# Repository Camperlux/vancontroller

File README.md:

# VanController

A 12 V campervan controller board: ESP32-S3 with 6 fused relays, 6 fused PWM dimmers, CAN, RS485, GPS, an accelerometer and 2 water-level inputs, plus a 3D-printable enclosure. Designed in KiCad 10.

| | |
|---|---|
| **Revision** | 0.3a |
| **Status** | Design complete (ERC and DRC clean). Prototype order with PCBWay under engineering review since 2026-10-06; see [docs/ORDER_LOG.md](docs/ORDER_LOG.md). Not yet verified on hardware. |
| **Board** | 230 × 135 mm, 4 layers (In1 = GND plane, In2 = +12 V plane), 1.6 mm, 1 oz copper, ENIG |
| **Enclosure** | 251 × 142 × 35 mm two-part print with mounting ears ([enclosure/](enclosure/)) |

## Features

- **Power:** 12 V input on M5 studs. 30 A ATO main fuse, bidirectional load-dump TVS, LM74700-Q1 ideal-diode reverse-polarity protection with 2 × CSD18540Q5B, TPS54360 buck to 5 V, AMS1117 to 3.3 V. Input voltage sensing.
- **6 relay outputs:** Omron G5LE 10 A, each with its own mini blade fuse, COM/NO/NC terminals (COM = fused +12 V by default), indicator LED and fuse-blown sensing. Any channel converts to a **dry contact** by removing its fuse and cutting a solder jumper ([DESIGN_SPEC.md §4](DESIGN_SPEC.md#dry-contact-mode-per-relay-channel)).
- **6 dimmer outputs:** 60 V logic-level MOSFETs (low side, PWM), 5 A mini blade fuse each, freewheel diode, fuse-blown sensing.
- **Comms:** CAN (TJA1051T/3) and RS485 (THVD1450), with jumper-selectable termination and fail-safe bias.
- **Sensors:** u-blox MAX-M10S GPS (u.FL active antenna), LIS3DH accelerometer, ADS1115 16-bit ADC with 2 water-level inputs (each jumper-selectable for resistive, 4-20 mA or 0-5 V senders).
- **MCU:** ESP32-S3-WROOM-1-N16 with native USB-C, BOOT/RESET buttons and a UART debug header. Wi-Fi/BLE antenna at the board edge, with no copper under it.
- **Terminals:** all 12 outputs along one edge on Phoenix MSTBA 5.08 mm pluggable headers.

## Documents

| Document | Contents |
|---|---|
| [DESIGN_SPEC.md](DESIGN_SPEC.md) | Design decisions, **GPIO map**, I2C addresses, terminal pinouts, PCB notes, open design checks, **firmware notes** |
| [docs/ORDER_LOG.md](docs/ORDER_LOG.md) | Manufacturing record: PCBWay quote and cart items, decisions (1 oz copper, ENIG, self-fitted through-hole parts), engineering Q&A, open items |
| [docs/VanController_schematic.pdf](docs/VanController_schematic.pdf) | Full schematic (19 pages) |
| [docs/VanController_assembly_top.pdf](docs/VanController_assembly_top.pdf) | Top-side assembly drawing with reference designators |
| [docs/](docs/) | Board and placement images, 3D renders |

## Repository layout

| Path | Contents |
|---|---|
| `VanController.kicad_pro`, `*.kicad_sch`, `VanController.kicad_pcb` | KiCad 10 project. Hierarchical schematic: root → Power, MCU, Relays (6 × `relay_channel`), Dimmers (6 × `dimmer_channel`), Comms, Sensors |
| `fab/` | Gerbers + drill (`gerbers/`, `VanController_gerbers.zip`), BOM, pick-and-place, board STEP model |
| `manufacturing/VanController_rev0.3_PCBWay/` | The order package sent to PCBWay: Gerbers, BOM with manufacturer part numbers (xlsx), centroid file, order notes, drawings, 3D model, optional enclosure print files |
| `enclosure/` | Fusion 360 enclosure script, print-ready STLs, assembly STEP with the PCB (run the script to recreate the Fusion design) |
| `tools/` | Python scripts that generated and finish the project (see below) |

## Ordering and building

1. **Order:** upload the files from `manufacturing/VanController_rev0.3_PCBWay/` (read `00_READ_ME_ORDER_NOTES.txt`), or rebuild the package with `python tools/make_order_package.py`. Settings used: 4 layers, 1.6 mm, **1 oz** copper (2 oz is not manufacturable with this design's 0.15 mm fine-pitch spacing), ENIG, SMD-only assembly.
2. **Through-hole parts** are fitted by hand: relays K1-K6, terminal headers, fuse holders F1-F13 and pin headers (47 per board). The relay, F1 and output terminal joints sit on large copper areas, so use a 60-80 W iron.
3. **Not fitted by the assembler:** blade fuses (size each to its load), jumper shunts (choose per [DESIGN_SPEC.md §4](DESIGN_SPEC.md#4-terminals)) and the M5 stud bolts for J1/J2.
4. **Enclosure:** print `enclosure/VanController_base.stl` and `VanController_lid.stl` in PETG or ASA (not PLA). Hardware: 8 × M3 heat-set inserts, 4 × M3×8 (lid), 4 × M3×6 (PCB), 2 × M16 cable glands, 1 × SMA bulkhead to u.FL pigtail.
5. **First power-up:** use a current-limited bench supply, check +5 V and +3V3, then fit fuses one output at a time. See [DESIGN_SPEC.md §7](DESIGN_SPEC.md#7-design-checks-and-cautions) for the thermal and load checks.

## How the design was generated

The schematic and board were generated by scripts, then routed and hand-fixed. **From now on, edit the design in KiCad.** The board contains hand fixes (around U9) that no script reproduces, so do not regenerate it.

| Script | Purpose | Overwrites |
|---|---|---|
| `tools/gen_schematic.py` | Builds every schematic sheet from the circuit tables in the script | all `.kicad_sch` |
| `tools/gen_pcb.py` (KiCad Python) | Builds the board from the netlist: footprints, placement, high-current copper, planes, plane fan-out vias | `VanController.kicad_pcb` |
| `tools/netclasses.py` | Writes net classes and design rules into `.kicad_pro` | net settings |
| Freerouting 1.9.0 | Autoroutes the exported DSN: `java -jar freerouting-1.9.0.jar -de vc.dsn -do vc.ses -mp 40 -mt 1` | — |
| `tools/finish_pcb.py` (KiCad Python) | Imports routes, adds outer GND pours, fills zones, tidies silkscreen | the board given |
| `tools/fix_pcb.py` (KiCad Python) | Fixes via drills, removes dangling router tails, refills zones | the board given |
| `tools/patch_pcb.py` (KiCad Python) | Hand fixes: MOSFET gate link on B.Cu, vias for stranded plane pads | the board given |
| `tools/patch_dry_contact.py` + `tools/strip_sj_courtyard.py` | Rev 0.3a: adds the SJ dry-contact jumpers to the routed board | `VanController.kicad_pcb` |
| `tools/make_fab.py` | Gerbers, drill, BOM, pick-and-place, STEP, PDFs | `fab/`, `docs/` |
| `tools/make_order_package.py` | Builds the PCBWay order package (xlsx BOM with MPNs, board-origin centroid, notes) | `manufacturing/` |
| `enclosure/VanControllerEnclosure/VanControllerEnclosure.py` | Fusion 360 script: builds base + lid, imports the PCB, exports STL/STEP/f3d into the `enclosure/` folder next to it | `enclosure/` outputs |

**Tool notes:**
- KiCad Python is `C:\Program Files\KiCad\10.0\bin\python.exe`.
- Freerouting is not in the repo: download `freerouting-1.9.0.jar` from the [Freerouting releases](https://github.com/freerouting/freerouting/releases) into `tools/freerouting/`. Use 1.9.0 with `-mt 1`: version 2.x ignores the pass limit from the command line, and multithreaded optimisation creates clearance errors.
- Before exporting the DSN, set the inner layers to power-plane type (`gen_pcb.py` does this), or Freerouting routes signals on them and splits the planes.

## Lessons learned (rev 0.3)

- Fan out SMD pads on plane nets (stub + via) before autorouting: unrouted connections fell from 499 to 5.
- Check that autorouted tracks don't cut high-current copper areas: an early route split one input MOSFET's sources off the input.
- 2 oz outer copper needs ≥ 6.5-8 mil spacing. Fine-pitch ICs at 0.15 mm force 1 oz.
- PCBWay wants ≥ 0.19 mm between pads for solder-mask dams. Below that, the mask is opened across the IC.
- KiCad Python: `PCB_VIA.GetWidth()` without a layer argument raises an invisible assert dialog that hangs the script. Use `GetWidth(pcbnew.F_Cu)`.

## Revision history

| Rev | Date | Changes |
|---|---|---|
| 0.1 | 2026-10-05 | Spec, GPIO map, hierarchical sheet skeleton |
| 0.2 | 2026-10-05 | Full schematic (ERC clean); first 169 × 135 mm placement |
| 0.3 | 2026-10-05/06 | 230 × 135 mm rectangular layout with all outputs on one edge; plane fan-out; routed (DRC clean); TCA9535 address changed to 0x21; enclosure; PCBWay order package and order submitted |
| 0.3a | 2026-10-14 | Dry-contact option: solder jumpers SJ1-SJ6 isolate the fuse-sense resistor from relay COM (`tools/patch_dry_contact.py`). Copper-only change: Gerbers updated, BOM and placement unchanged |

## Licence

Copyright (c) 2026 Camperlux. **Free for non-commercial use.** The hardware design, manufacturing files and documentation are under [CC BY-NC-SA 4.0](LICENSE-docs.txt), and the scripts are under the [PolyForm Noncommercial License 1.0.0](LICENSE.md). Commercial use, including selling boards, kits or products based on this design, needs a licence from Camperlux. See [NOTICE.md](NOTICE.md) for details and third-party parts.

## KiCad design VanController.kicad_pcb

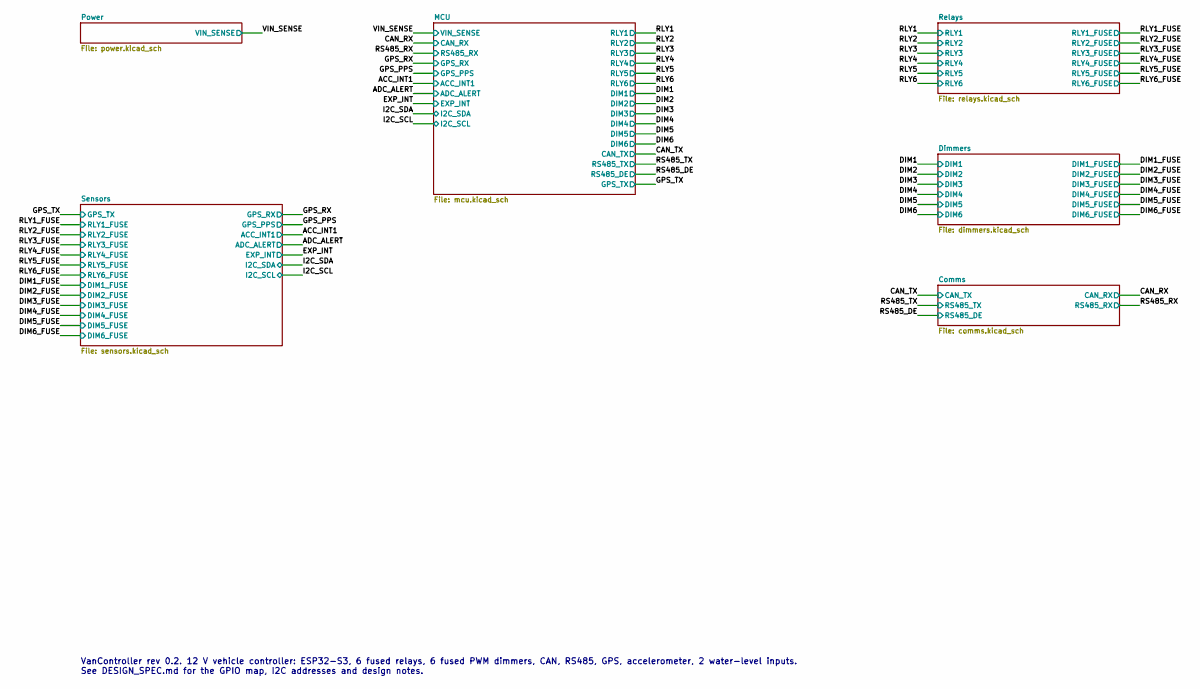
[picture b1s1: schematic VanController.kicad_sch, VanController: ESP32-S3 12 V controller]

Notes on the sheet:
VanController rev 0.2. 12 V vehicle controller: ESP32-S3, 6 fused relays, 6 fused PWM dimmers, CAN, RS485, GPS, accelerometer, 2 water-level inputs. See DESIGN_SPEC.md for the GPIO map, I2C addresses and design notes.

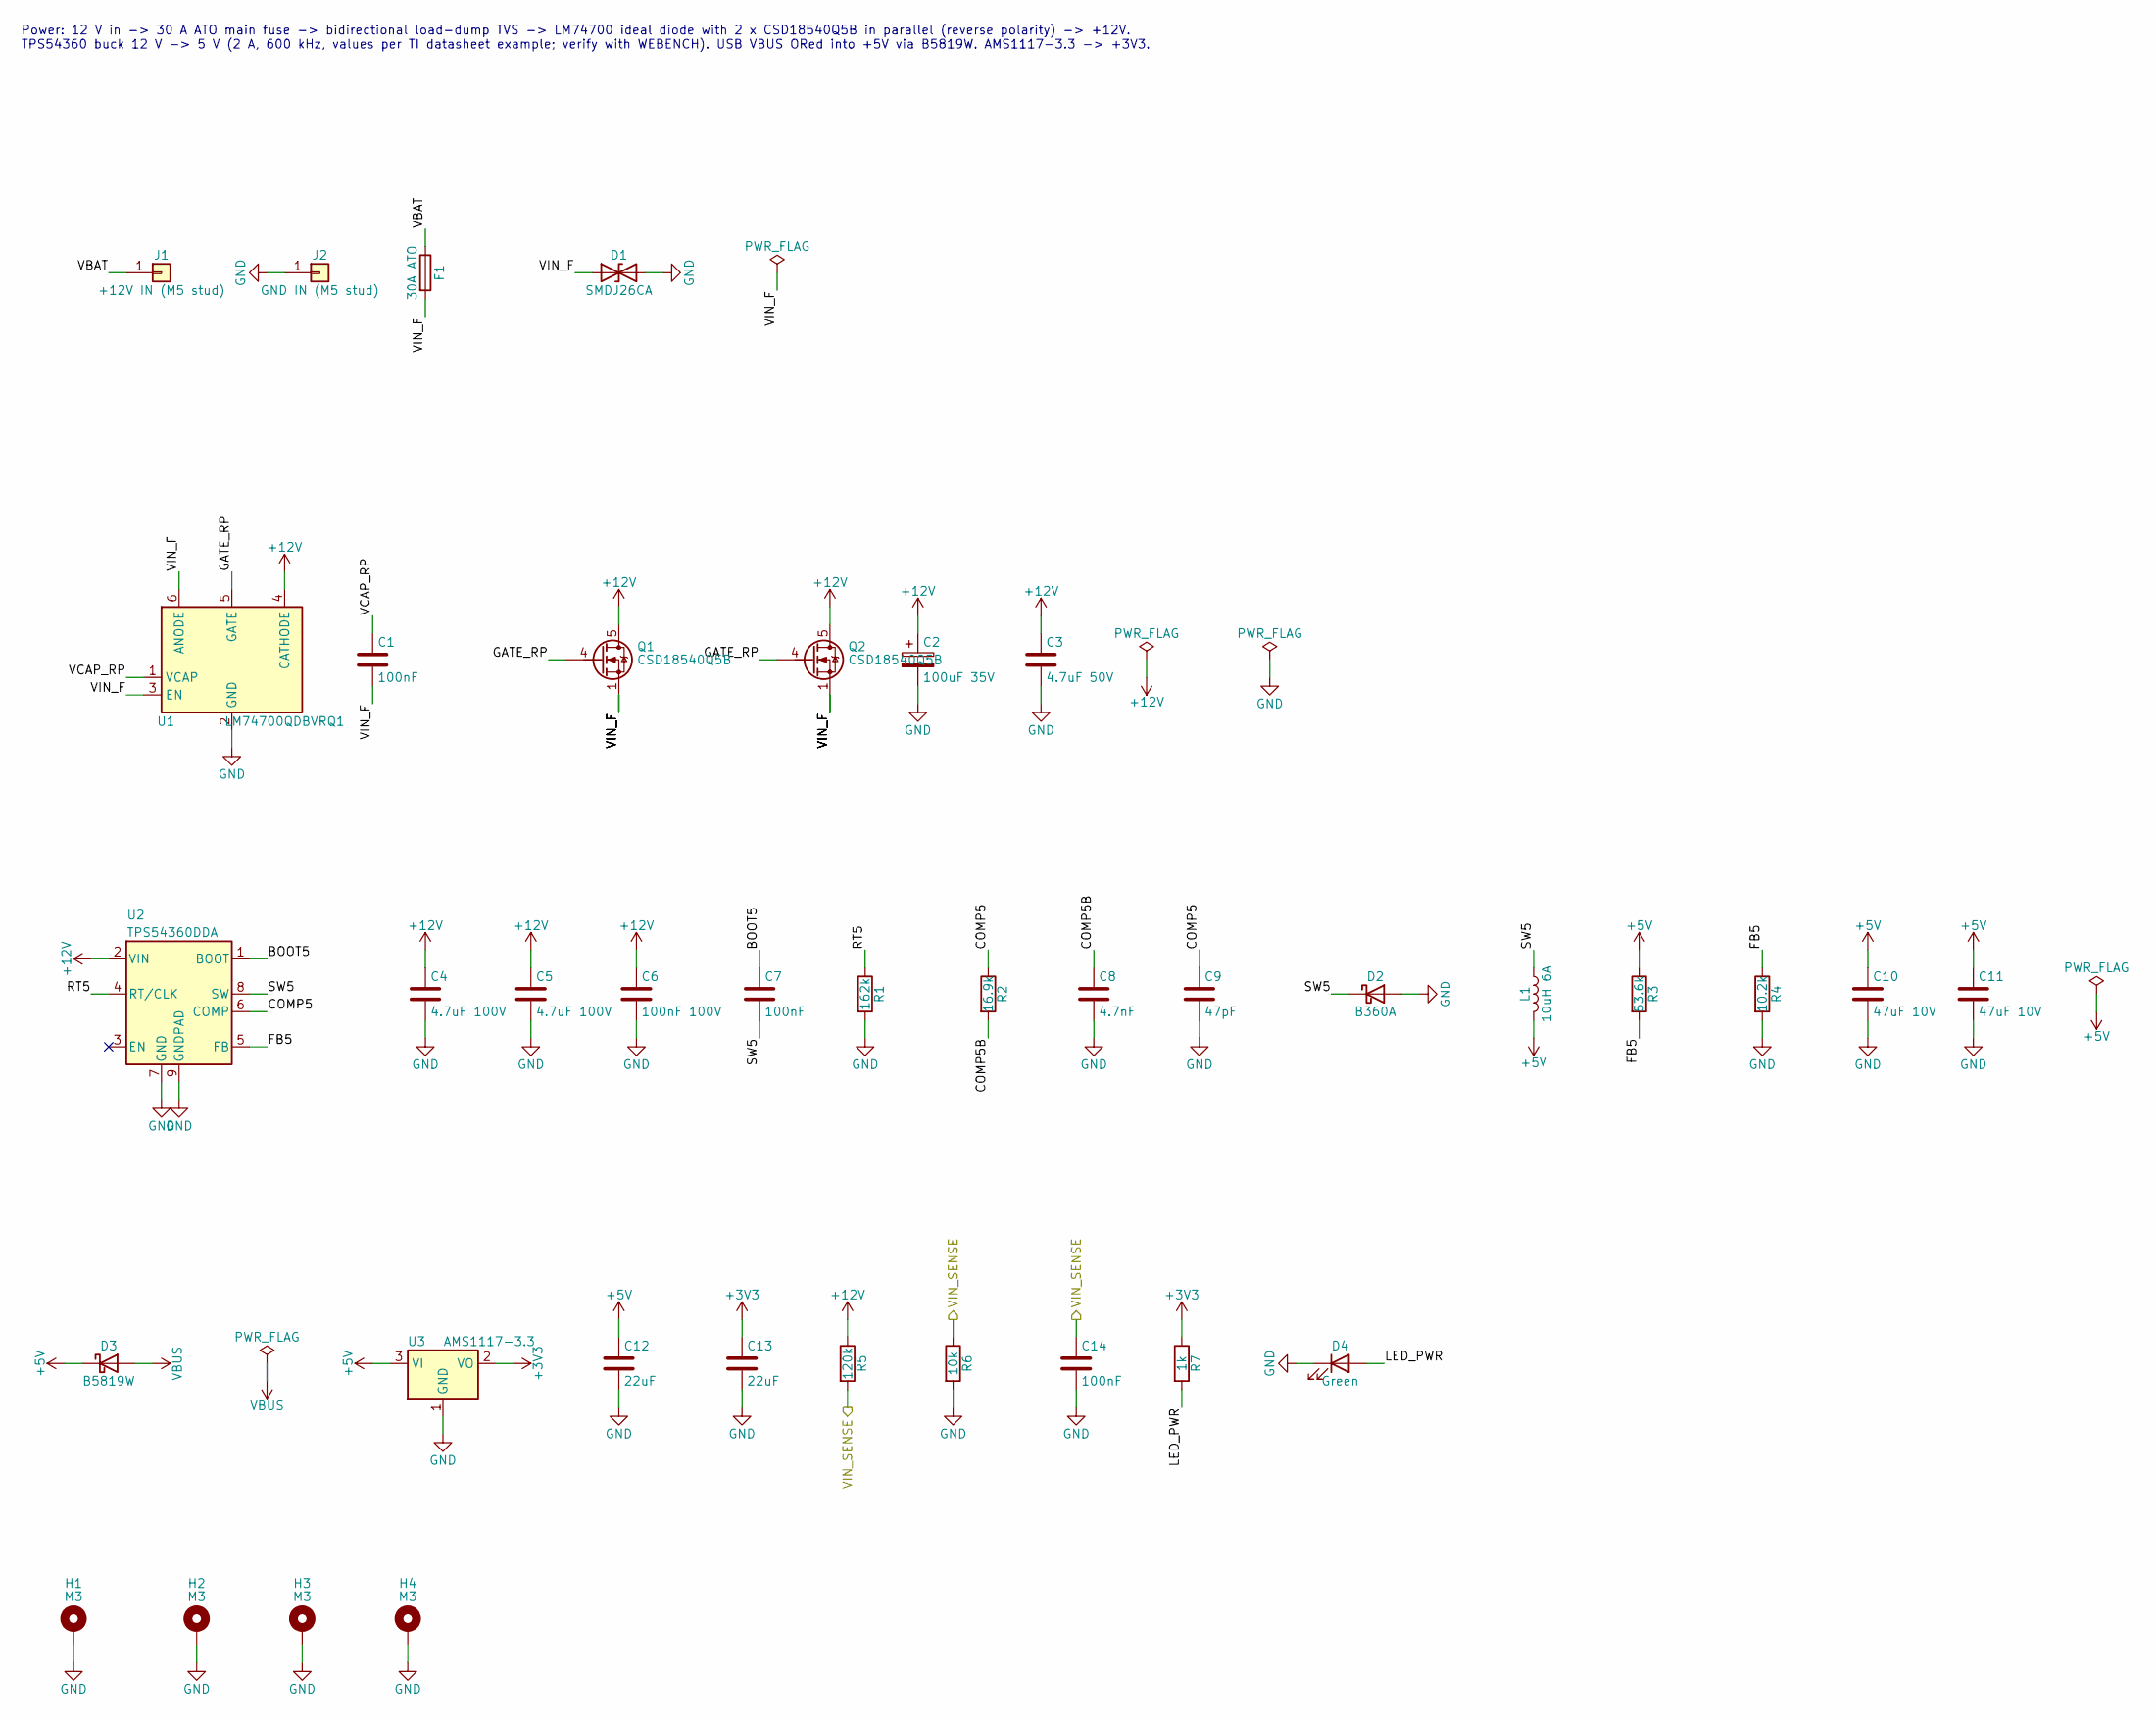
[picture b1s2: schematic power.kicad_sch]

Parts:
C1, C7, C14: 100nF; C_0603_1608Metric
C2: 100uF 35V; CP_Elec_8x10
C3: 4.7uF 50V; C_1210_3225Metric
C4, C5: 4.7uF 100V; C_1210_3225Metric
C6: 100nF 100V; C_0603_1608Metric
C8: 4.7nF; C_0603_1608Metric
C9: 47pF; C_0603_1608Metric
C10, C11: 47uF 10V; C_1210_3225Metric
C12, C13: 22uF; C_0805_2012Metric
D1: SMDJ26CA; D_SMC
D2: B360A; D_SMA
D3: B5819W; D_SOD-123
D4: Green; LED_0603_1608Metric
F1: 30A ATO; FuseHolder_Blade_ATO_Littelfuse_FLR_178.6165; MPN Littelfuse FLR 178.6165 + 30 A ATO fuse
H1, H2, H3, H4: M3; MountingHole_3.2mm_M3_Pad_Via
J1: +12V IN (M5 stud); MountingHole_5.3mm_M5_DIN965_Pad
J2: GND IN (M5 stud); MountingHole_5.3mm_M5_DIN965_Pad
L1: 10uH 6A; L_Bourns_SRP1038C_10.0x10.0mm; MPN Bourns SRP1038C-100M
Q1, Q2: CSD18540Q5B; TDSON-8-1
R1: 162k; R_0603_1608Metric
R2: 16.9k; R_0603_1608Metric
R3: 53.6k; R_0603_1608Metric
R4: 10.2k; R_0603_1608Metric
R5: 120k; R_0603_1608Metric
R6: 10k; R_0603_1608Metric
R7: 1k; R_0603_1608Metric
U1: LM74700QDBVRQ1; SOT-23-6
U2: TPS54360DDA; TI_SO-PowerPAD-8_ThermalVias
U3: AMS1117-3.3; SOT-223-3_TabPin2

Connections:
+3V3: C13.1, R7.1, U3.2 (VO); also elsewhere on the board
+5V: C10.1, C11.1, C12.1, D3.1 (K), L1.2, R3.1, U3.3 (VI); also elsewhere on the board
+12V: C2.1, C3.1, C4.1, C5.1, C6.1, Q1.5 (D), Q2.5 (D), R5.1, U1.4 (CATHODE), U2.2 (VIN); also elsewhere on the board
/Power/BOOT5: C7.1, U2.1 (BOOT)
/Power/COMP5: C9.1, R2.1, U2.6 (COMP)
/Power/COMP5B: C8.1, R2.2
/Power/FB5: R3.2, R4.1, U2.5 (FB)
/Power/GATE_RP: Q1.4 (G), Q2.4 (G), U1.5 (GATE)
/Power/LED_PWR: D4.2 (A), R7.2
/Power/RT5: R1.1, U2.4 (RT/CLK)
/Power/SW5: C7.2, D2.1 (K), L1.1, U2.8 (SW)
/Power/VBAT: F1.1, J1.1
/Power/VCAP_RP: C1.1, U1.1 (VCAP)
/Power/VIN_F: C1.2, D1.1 (A1), F1.2, Q1.1 (S), Q1.2 (S), Q1.3 (S), Q2.1 (S), Q2.2 (S), Q2.3 (S), U1.3 (EN), U1.6 (ANODE)
/VIN_SENSE: C14.1, R5.2, R6.1; also elsewhere on the board
GND: C2.2, C3.2, C4.2, C5.2, C6.2, C8.2, C9.2, C10.2, C11.2, C12.2, C13.2, C14.2, D1.2 (A2), D2.2 (A), D4.1 (K), H1.1, H2.1, H3.1, H4.1, J2.1, R1.2, R4.2, R6.2, U1.2 (GND), U2.7 (GND), U2.9 (GNDPAD), U3.1 (GND); also elsewhere on the board
VBUS: D3.2 (A); also elsewhere on the board

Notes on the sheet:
Power: 12 V in -> 30 A ATO main fuse -> bidirectional load-dump TVS -> LM74700 ideal diode with 2 x CSD18540Q5B in parallel (reverse polarity) -> +12V. TPS54360 buck 12 V -> 5 V (2 A, 600 kHz, values per TI datasheet example; verify with WEBENCH). USB VBUS ORed into +5V via B5819W. AMS1117-3.3 -> +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

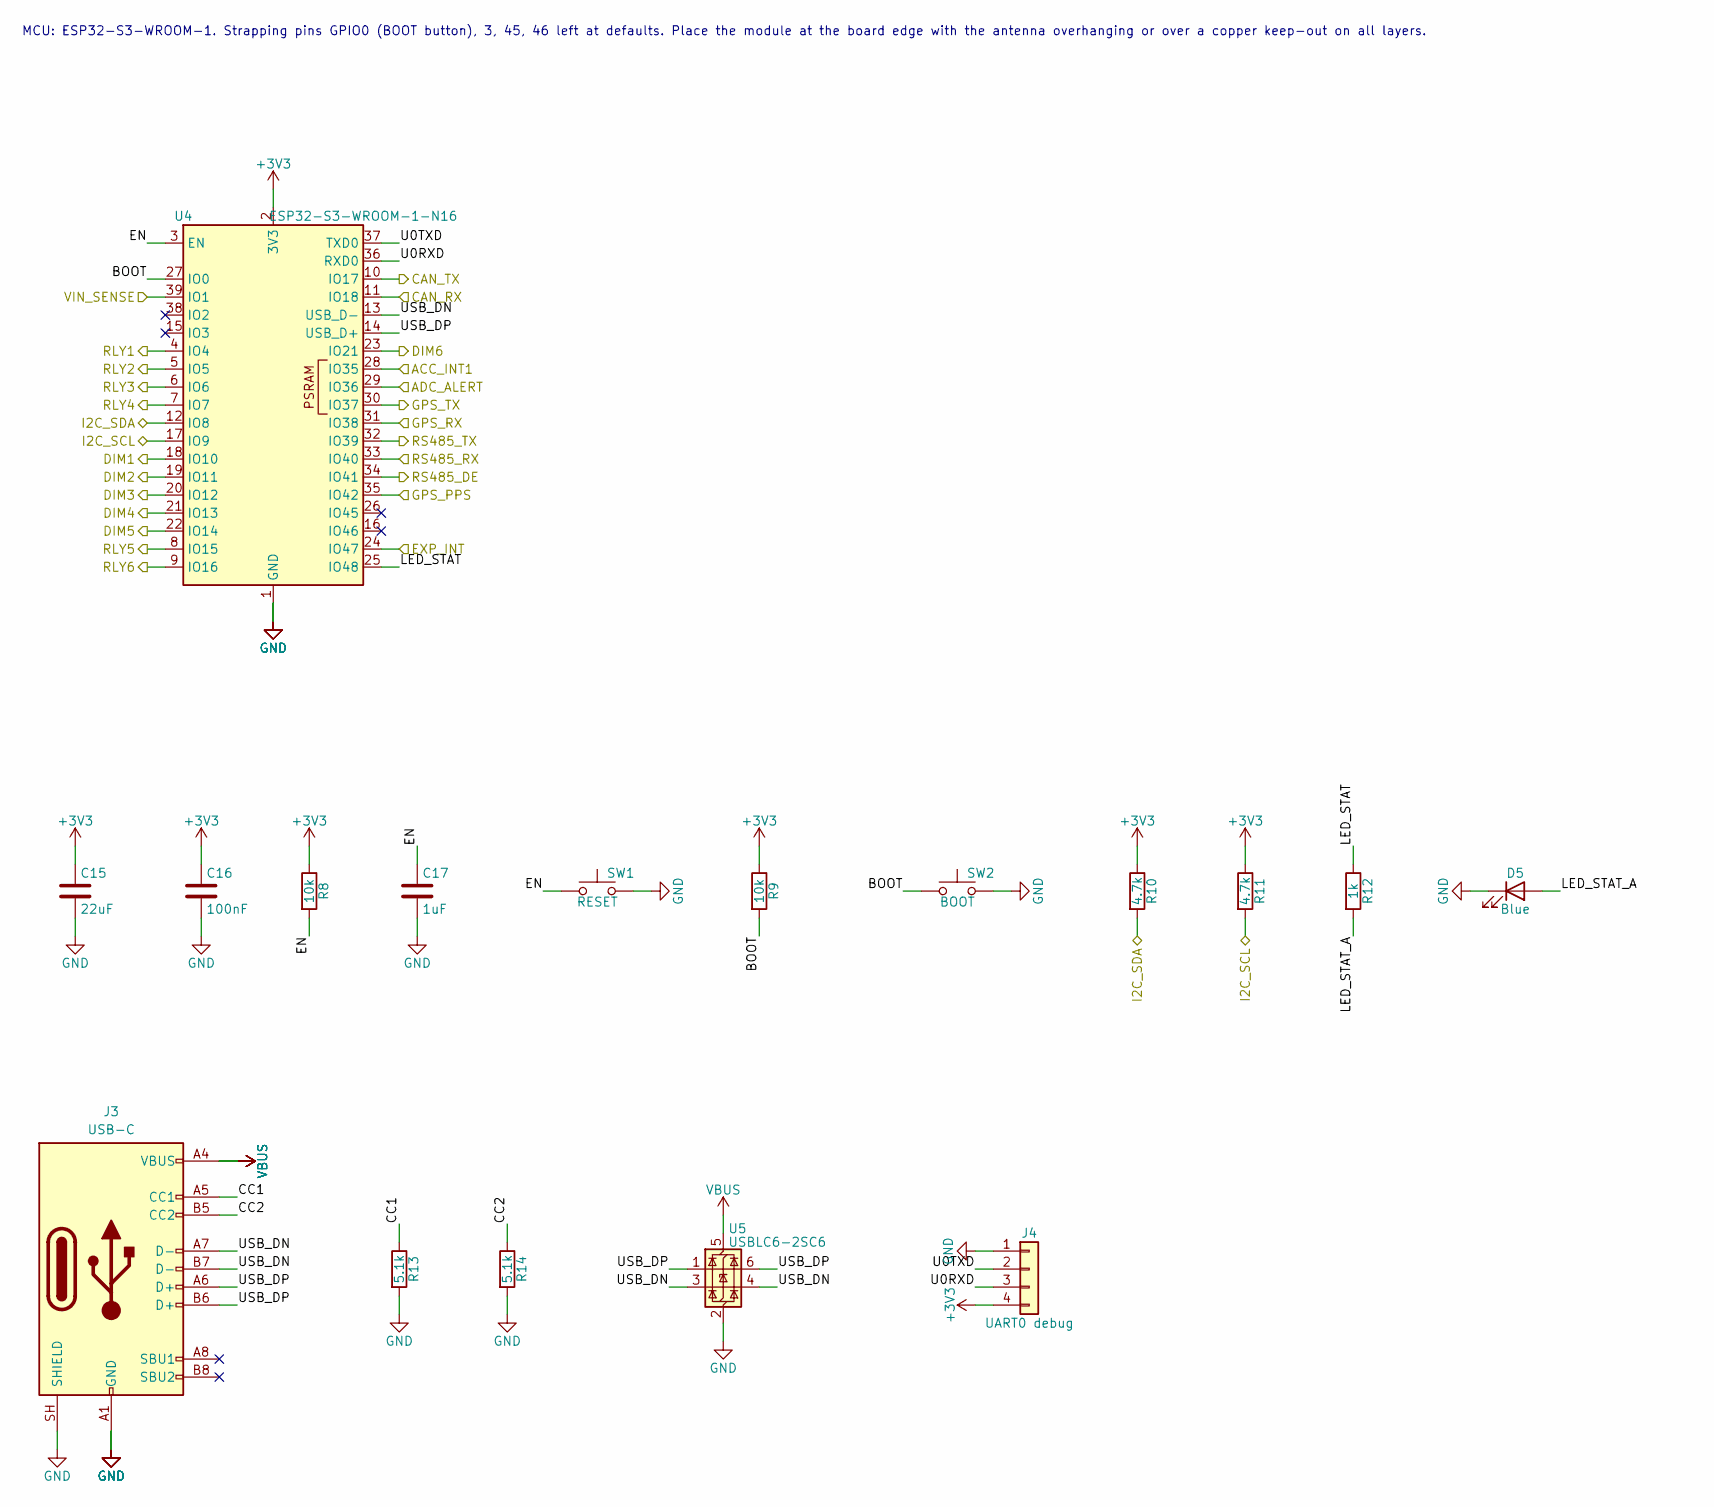
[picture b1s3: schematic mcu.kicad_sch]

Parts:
C15: 22uF; C_0805_2012Metric
C16: 100nF; C_0603_1608Metric
C17: 1uF; C_0603_1608Metric
D5: Blue; LED_0603_1608Metric
J3: USB-C; USB_C_Receptacle_GCT_USB4105-xx-A_16P_TopMnt_Horizontal
J4: UART0 debug; PinHeader_1x04_P2.54mm_Vertical
R8, R9: 10k; R_0603_1608Metric
R10, R11: 4.7k; R_0603_1608Metric
R12: 1k; R_0603_1608Metric
R13, R14: 5.1k; R_0603_1608Metric
SW1: RESET; SW_SPST_B3U-1000P
SW2: BOOT; SW_SPST_B3U-1000P
U4: ESP32-S3-WROOM-1-N16; ESP32-S3-WROOM-1
U5: USBLC6-2SC6; SOT-23-6

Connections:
+3V3: C15.1, C16.1, J4.4, R8.1, R9.1, R10.1, R11.1, U4.2 (3V3); also elsewhere on the board
/ACC_INT1: U4.28 (IO35); also elsewhere on the board
/ADC_ALERT: U4.29 (IO36); also elsewhere on the board
/CAN_RX: U4.11 (IO18); also elsewhere on the board
/CAN_TX: U4.10 (IO17); also elsewhere on the board
/DIM1: U4.18 (IO10); also elsewhere on the board
/DIM2: U4.19 (IO11); also elsewhere on the board
/DIM3: U4.20 (IO12); also elsewhere on the board
/DIM4: U4.21 (IO13); also elsewhere on the board
/DIM5: U4.22 (IO14); also elsewhere on the board
/DIM6: U4.23 (IO21); also elsewhere on the board
/EXP_INT: U4.24 (IO47); also elsewhere on the board
/GPS_PPS: U4.35 (IO42); also elsewhere on the board
/GPS_RX: U4.31 (IO38); also elsewhere on the board
/GPS_TX: U4.30 (IO37); also elsewhere on the board
/I2C_SCL: R11.2, U4.17 (IO9); also elsewhere on the board
/I2C_SDA: R10.2, U4.12 (IO8); also elsewhere on the board
/MCU/BOOT: R9.2, SW2.1, U4.27 (IO0)
/MCU/CC1: J3.A5 (CC1), R13.1
/MCU/CC2: J3.B5 (CC2), R14.1
/MCU/EN: C17.1, R8.2, SW1.1, U4.3 (EN)
/MCU/LED_STAT: R12.1, U4.25 (IO48)
/MCU/LED_STAT_A: D5.2 (A), R12.2
/MCU/U0RXD: J4.3, U4.36 (RXD0)
/MCU/U0TXD: J4.2, U4.37 (TXD0)
/MCU/USB_DN: J3.A7 (D-), J3.B7 (D-), U4.13 (USB_D-), U5.3 (I/O2), U5.4 (I/O2)
/MCU/USB_DP: J3.A6 (D+), J3.B6 (D+), U4.14 (USB_D+), U5.1 (I/O1), U5.6 (I/O1)
/RLY1: U4.4 (IO4); also elsewhere on the board
/RLY2: U4.5 (IO5); also elsewhere on the board
/RLY3: U4.6 (IO6); also elsewhere on the board
/RLY4: U4.7 (IO7); also elsewhere on the board
/RLY5: U4.8 (IO15); also elsewhere on the board
/RLY6: U4.9 (IO16); also elsewhere on the board
/RS485_DE: U4.34 (IO41); also elsewhere on the board
/RS485_RX: U4.33 (IO40); also elsewhere on the board
/RS485_TX: U4.32 (IO39); also elsewhere on the board
/VIN_SENSE: U4.39 (IO1); also elsewhere on the board
GND: C15.2, C16.2, C17.2, D5.1 (K), J3.A1 (GND), J3.A12 (GND), J3.B1 (GND), J3.B12 (GND), J3.SH (SHIELD), J4.1, R13.2, R14.2, SW1.2, SW2.2, U4.1 (GND), U4.40 (GND), U4.41 (GND), U5.2 (GND); also elsewhere on the board
VBUS: J3.A4 (VBUS), J3.A9 (VBUS), J3.B4 (VBUS), J3.B9 (VBUS), U5.5 (VBUS); also elsewhere on the board

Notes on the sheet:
MCU: ESP32-S3-WROOM-1. Strapping pins GPIO0 (BOOT button), 3, 45, 46 left at defaults. Place the module at the board edge with the antenna overhanging or over a copper keep-out on all layers.

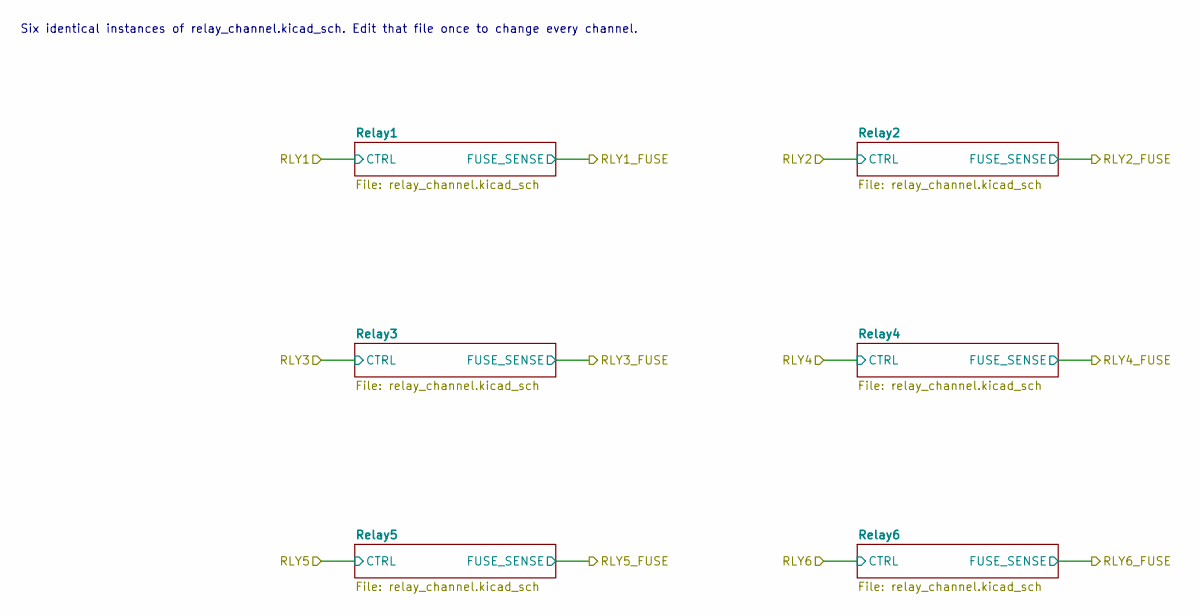
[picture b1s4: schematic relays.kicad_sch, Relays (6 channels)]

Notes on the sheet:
Six identical instances of relay_channel.kicad_sch. Edit that file once to change every channel.

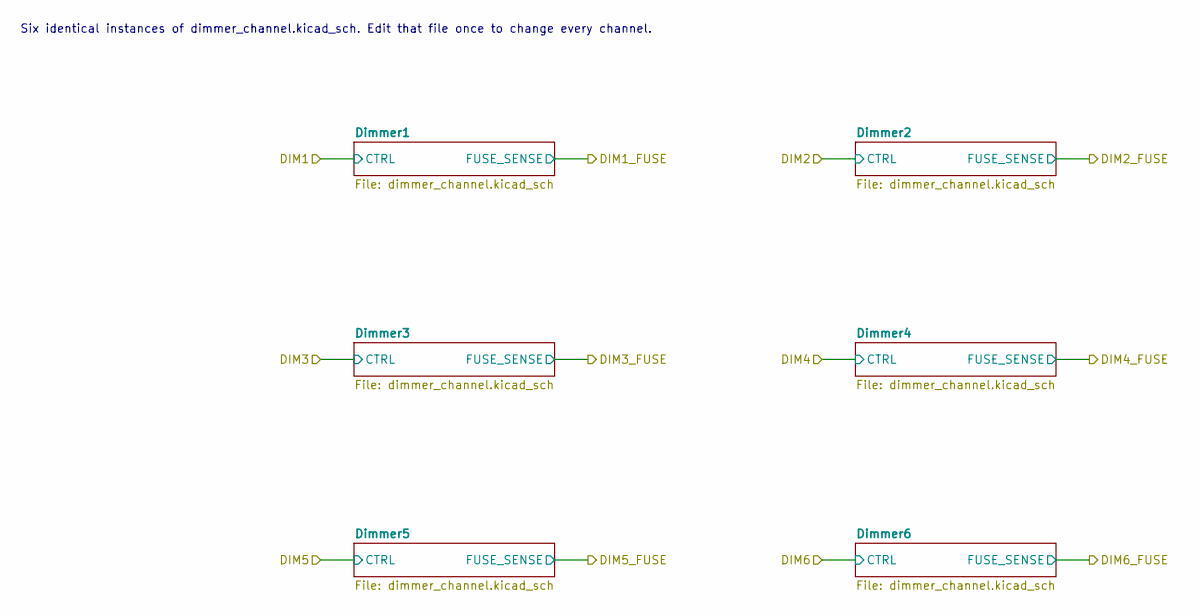
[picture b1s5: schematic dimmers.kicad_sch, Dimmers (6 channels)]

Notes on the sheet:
Six identical instances of dimmer_channel.kicad_sch. Edit that file once to change every channel.

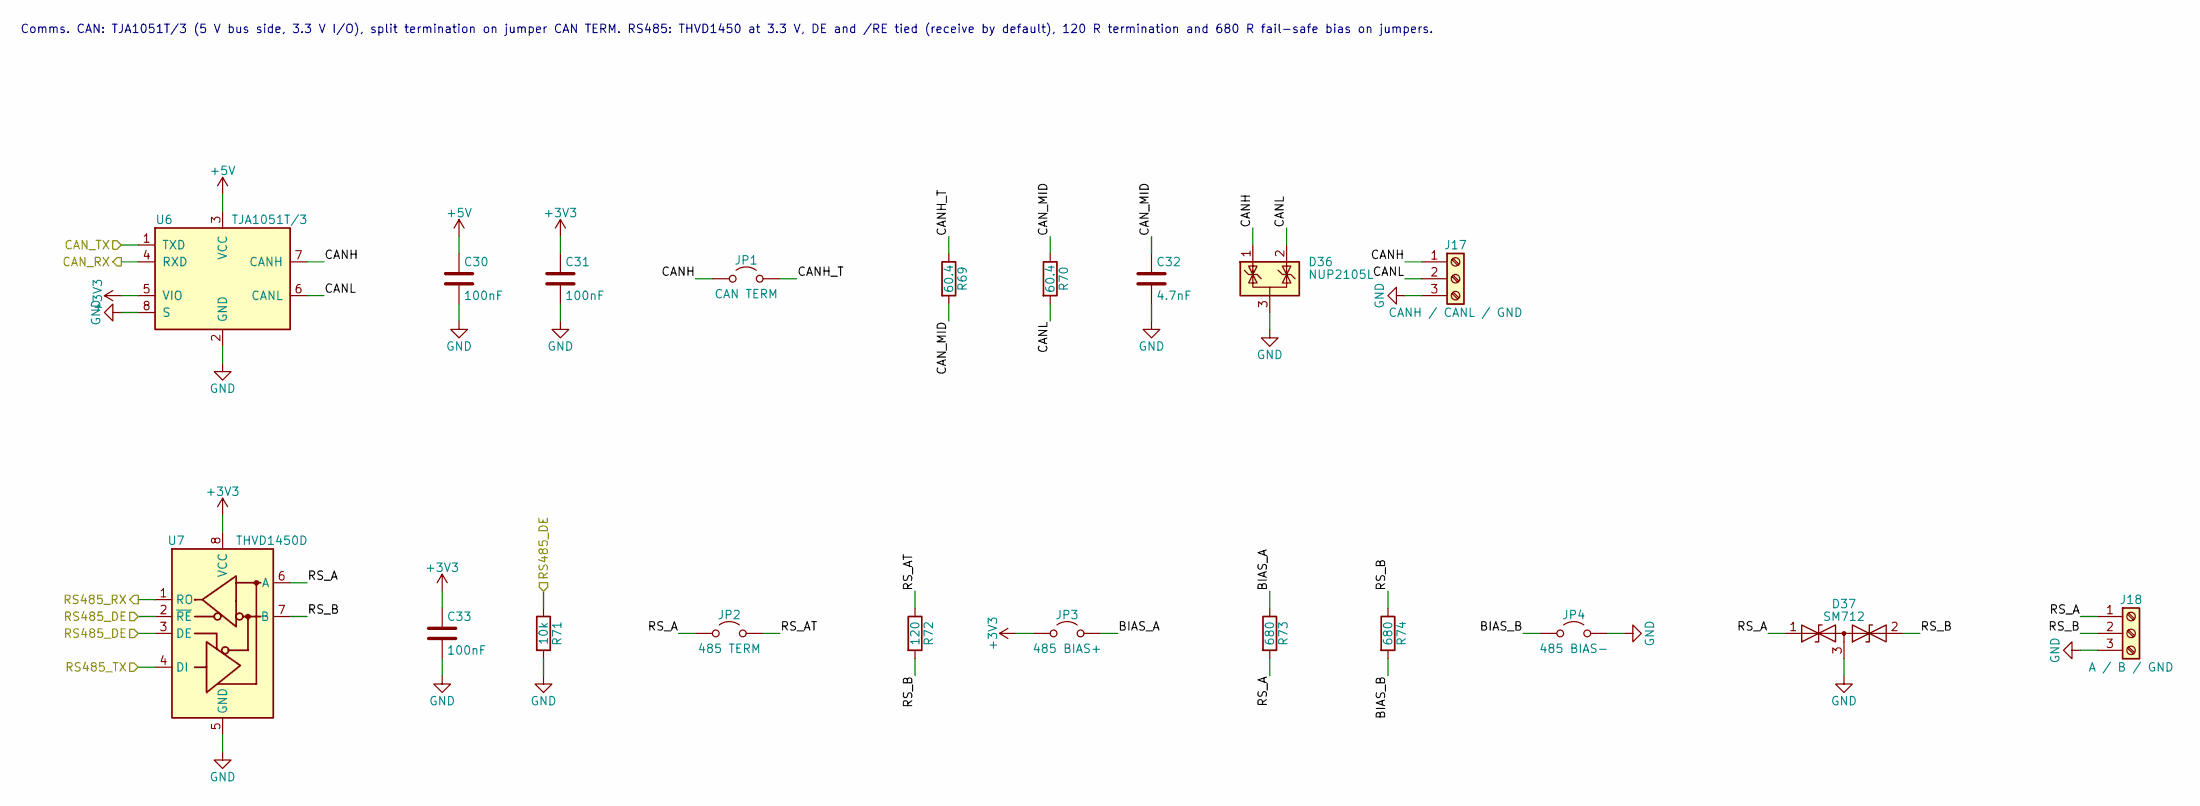
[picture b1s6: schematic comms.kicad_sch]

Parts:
C30, C31, C33: 100nF; C_0603_1608Metric
C32: 4.7nF; C_0603_1608Metric
D36: NUP2105L; SOT-23
D37: SM712; SOT-23
J17: CANH / CANL / GND; PhoenixContact_MSTBA_2,5_3-G-5,08_1x03_P5.08mm_Horizontal; MPN Phoenix MSTBA 2,5/3-G-5,08 + MSTB 2,5/3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
J18: A / B / GND; PhoenixContact_MSTBA_2,5_3-G-5,08_1x03_P5.08mm_Horizontal; MPN Phoenix MSTBA 2,5/3-G-5,08 + MSTB 2,5/3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
JP1: CAN TERM; PinHeader_1x02_P2.54mm_Vertical
JP2: 485 TERM; PinHeader_1x02_P2.54mm_Vertical
JP3: 485 BIAS+; PinHeader_1x02_P2.54mm_Vertical
JP4: 485 BIAS-; PinHeader_1x02_P2.54mm_Vertical
R69, R70: 60.4; R_0603_1608Metric
R71: 10k; R_0603_1608Metric
R72: 120; R_0603_1608Metric
R73, R74: 680; R_0603_1608Metric
U6: TJA1051T/3; SOIC-8_3.9x4.9mm_P1.27mm
U7: THVD1450D; SOIC-8_3.9x4.9mm_P1.27mm

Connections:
+3V3: C31.1, C33.1, JP3.1 (A), U6.5 (VIO), U7.8 (VCC); also elsewhere on the board
+5V: C30.1, U6.3 (VCC); also elsewhere on the board
/CAN_RX: U6.4 (RXD); also elsewhere on the board
/CAN_TX: U6.1 (TXD); also elsewhere on the board
/Comms/BIAS_A: JP3.2 (B), R73.1
/Comms/BIAS_B: JP4.1 (A), R74.2
/Comms/CANH: D36.1 (K), J17.1, JP1.1 (A), U6.7 (CANH)
/Comms/CANH_T: JP1.2 (B), R69.1
/Comms/CANL: D36.2 (K), J17.2, R70.2, U6.6 (CANL)
/Comms/CAN_MID: C32.1, R69.2, R70.1
/Comms/RS_A: D37.1 (A1), J18.1, JP2.1 (A), R73.2, U7.6 (A)
/Comms/RS_AT: JP2.2 (B), R72.1
/Comms/RS_B: D37.2 (A2), J18.2, R72.2, R74.1, U7.7 (B)
/RS485_DE: R71.1, U7.2 (~RE), U7.3 (DE); also elsewhere on the board
/RS485_RX: U7.1 (RO); also elsewhere on the board
/RS485_TX: U7.4 (DI); also elsewhere on the board
GND: C30.2, C31.2, C32.2, C33.2, D36.3 (A), D37.3 (common), J17.3, J18.3, JP4.2 (B), R71.2, U6.2 (GND), U6.8 (S), U7.5 (GND); also elsewhere on the board

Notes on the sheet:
Comms. CAN: TJA1051T/3 (5 V bus side, 3.3 V I/O), split termination on jumper CAN TERM. RS485: THVD1450 at 3.3 V, DE and /RE tied (receive by default), 120 R termination and 680 R fail-safe bias on jumpers.
